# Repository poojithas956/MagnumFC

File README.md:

# MagnumFC

MagnumFC is my 30 × 30 mm flight-controller design, built in KiCad around an STM32F722RETx. Honestly? This project has been such a fun rabbit hole. I wanted to build a compact FPV controller that felt useful, clean, and a bit more intentional than a random stack of boards shoved together with duct-tape energy.

The idea is simple but kinda cool: keep the board small, give the IMU and power rails proper attention, and make a design that actually looks like it could become something real. Lowkey, I’m hyped about it because this is the kind of hardware project that turns into a whole obsession once the schematic starts to come together.

## Why I built this

I wanted a flight-controller board that felt compact without becoming a mess of routing and half-documented shortcuts. The plan was to include the essentials:

- STM32F722 main controller
- ICM-42688-P IMU
- BMP388 barometer
- ESP32-C3 coprocessor
- USB-C connection
- analog OSD support
- separate 5 V and 9 V supply rails

It’s the kind of project that feels slightly chaotic in the best way. You start with a few part choices, a rough concept, and then suddenly you’re deep in power rails, pin assignments, and the weird little details that decide whether a board is actually usable or just a pretty render.

## Design overview

| Component or section | Intended role |
| --- | --- |
| STM32F722RETx | Main flight-controller MCU |
| ICM-42688-P | SPI gyroscope and accelerometer |
| BMP388 | Barometer |
| ESP32-C3 | Wireless-connectivity coprocessor |
| W25N04KVZEIR | NAND flash shown in the schematic and PCB; confirm device support before enabling it in firmware |
| MP9943GQ-Z × 2 | Switching 9 V and 5 V rails |
| AP7361C and NCP167 | Separate digital and analog 3.3 V rails, as represented in the design |
| AT7456E | Analog OSD circuitry |
| USB-C | USB connection to the flight controller |

## Board renders

These images are KiCad renders and design screenshots, not photos of a manufactured board. So yes, they look sick, but they’re still just the design phase, not a fully proven hardware build.

More circuit and layout screenshots are in [`Screenshots/`](Screenshots/). The schematic is also available as [`docs/sch.pdf`](docs/sch.pdf).

## Firmware note

The files under [`firmware/`](firmware/) are an early Betaflight target configuration draft, not a compiled firmware image. That part is intentionally unfinished. I left motor output and onboard flash configuration unresolved instead of pretending everything is fine when it’s not.

## Repo structure

- [`PCB/`](PCB/) — KiCad schematic, PCB layout, custom libraries, and manufacturing exports
- [`production/`](production/) — BOM, placement, designators, netlist, and fabrication package
- [`firmware/`](firmware/) — early Betaflight target draft and validation notes
- [`Screenshots/`](Screenshots/) — design and layout images
- [`docs/`](docs/) — schematic PDF
- [`JOURNAL.md`](JOURNAL.md) — work journal and design notes

## LICENSE

MIT

### Happy forging!

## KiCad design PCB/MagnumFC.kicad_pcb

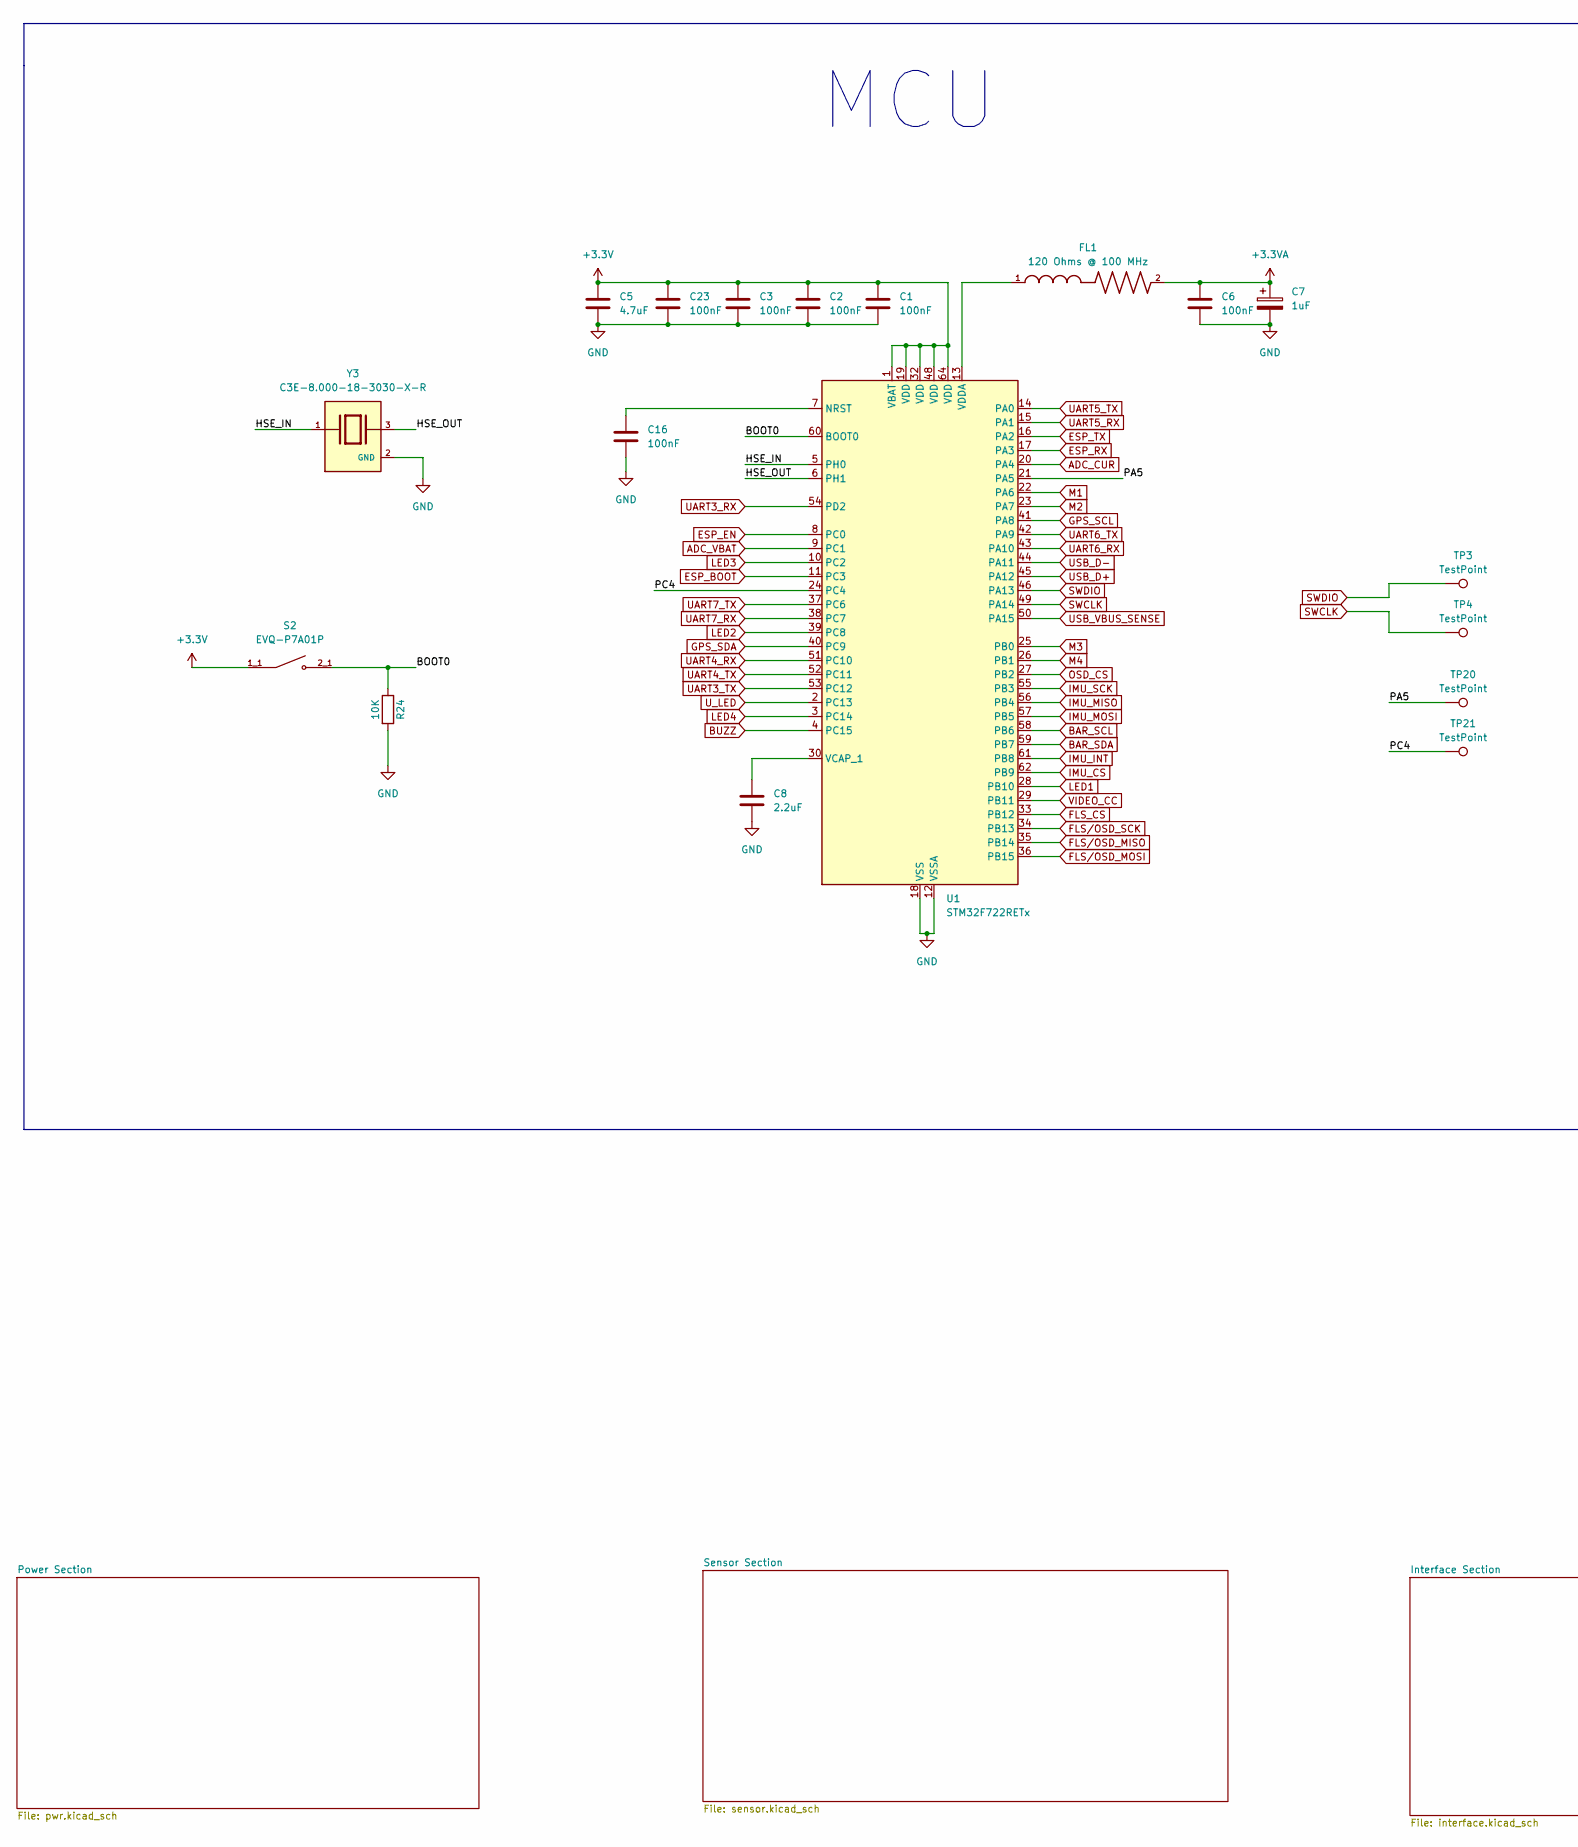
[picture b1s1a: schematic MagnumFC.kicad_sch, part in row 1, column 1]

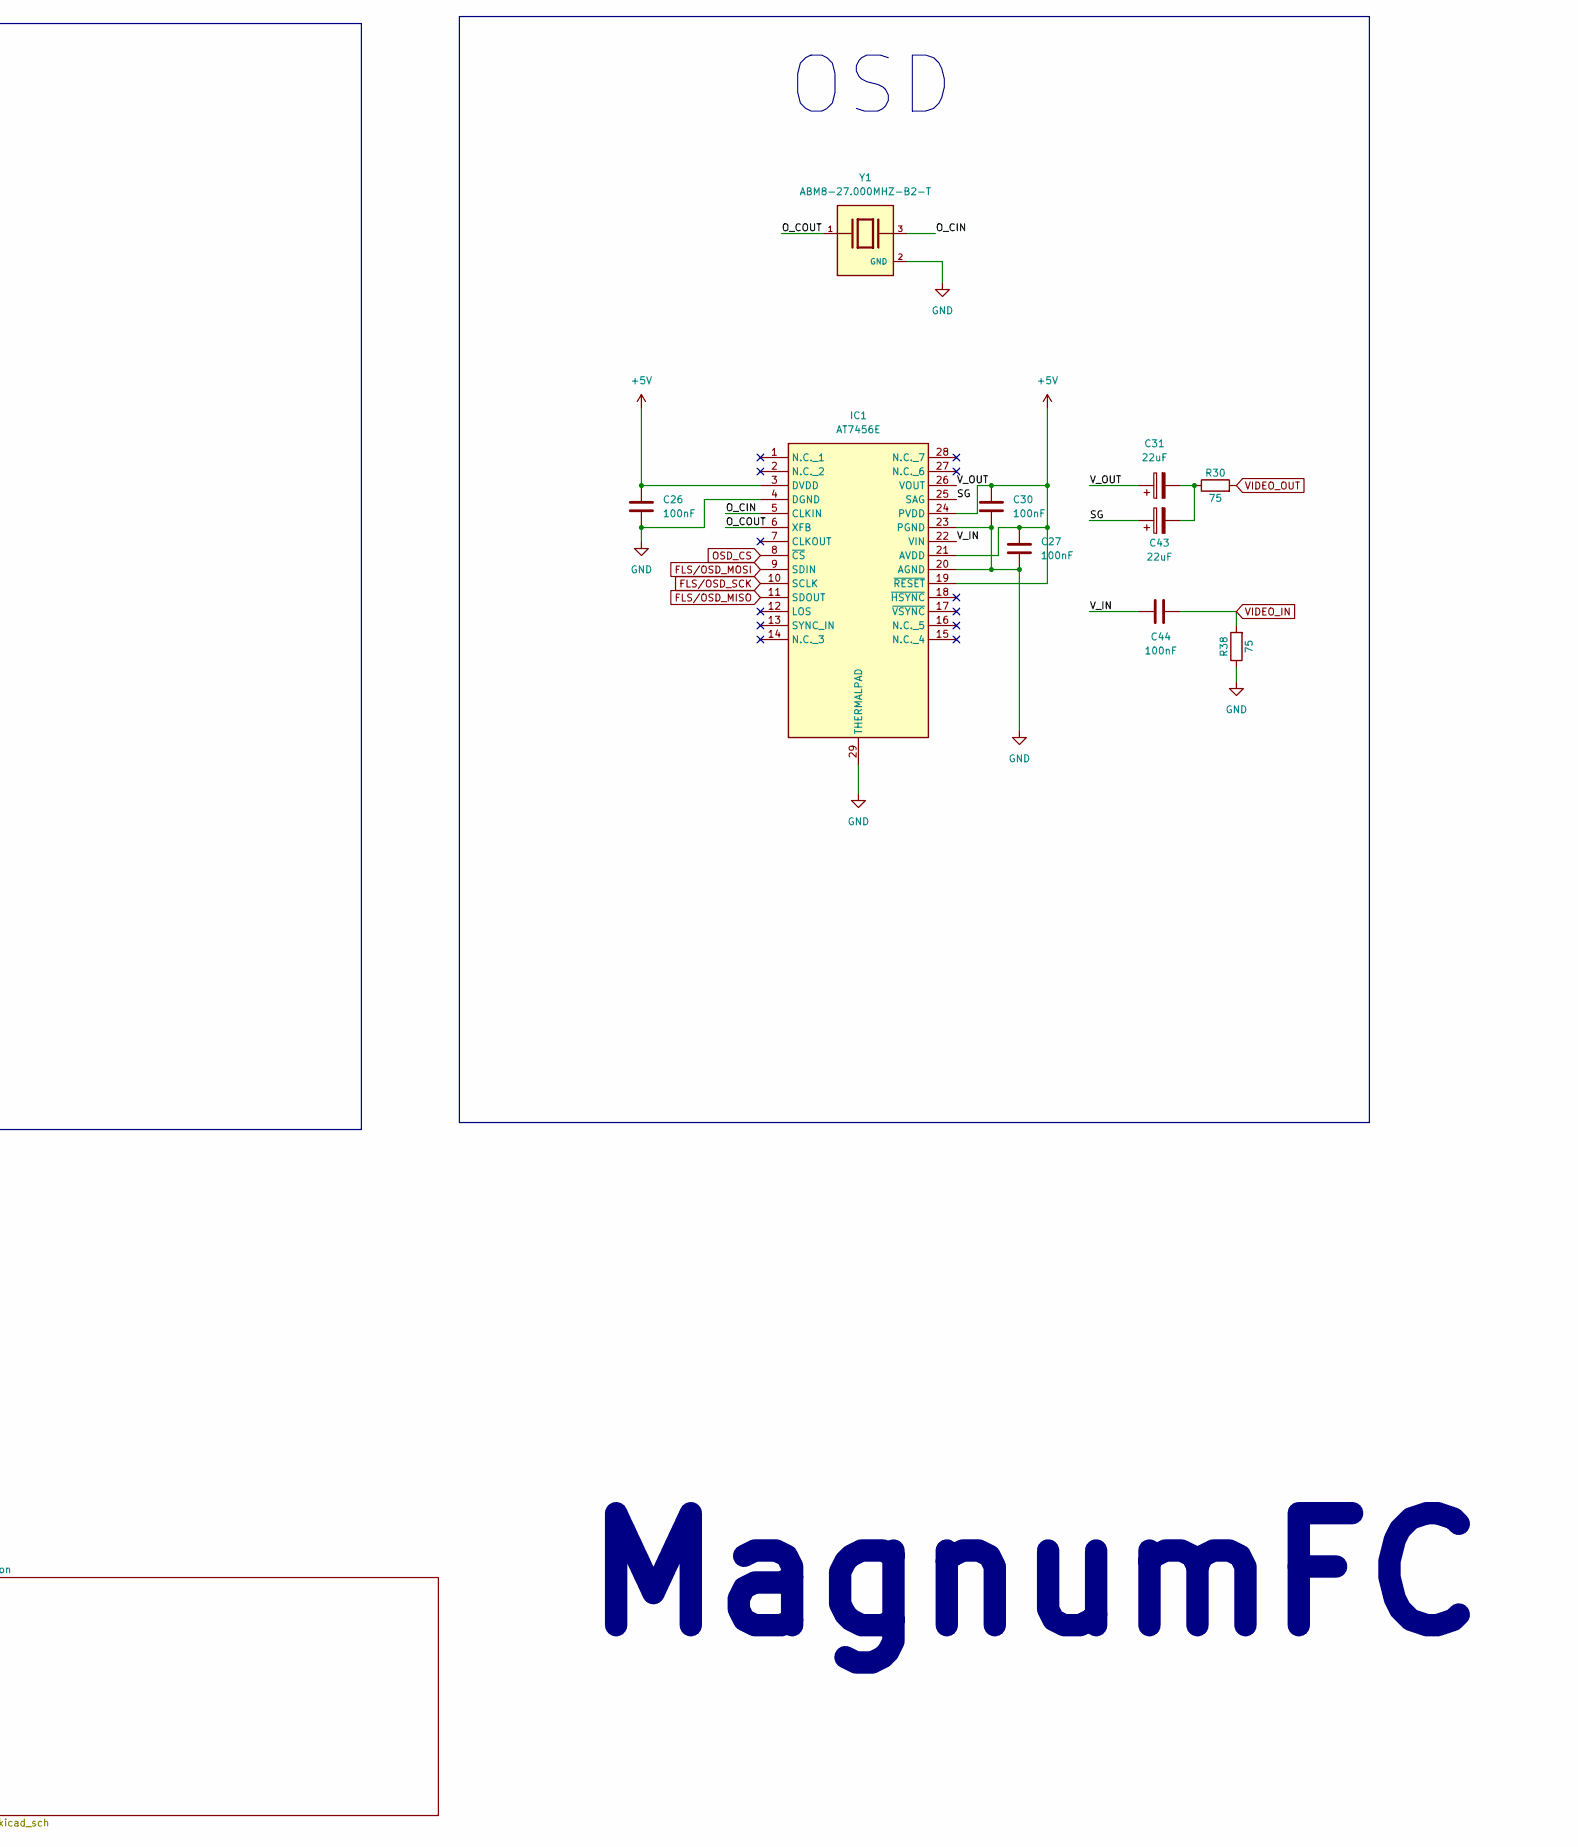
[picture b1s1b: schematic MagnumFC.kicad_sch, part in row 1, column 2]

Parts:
C1, C2, C3, C6, C16, C23, C26, C27, C30, C44: 100nF; C_0402_1005Metric; MANUFACTURER PART NUMBER CL05A104KA5NNNC; LCSC C100072
C5: 4.7uF; C_0603_1608Metric; MANUFACTURER PART NUMBER CL10A475KO8NNNC; LCSC C19666
C7: 1uF; C_0805_2012Metric; MANUFACTURER PART NUMBER CL21B105KOFNNNE; LCSC C24123
C8: 2.2uF; C_0402_1005Metric; MANUFACTURER PART NUMBER CL05A225KP5NSNC; LCSC C107369
C31, C43: 22uF; C_0805_2012Metric; MANUFACTURER PART NUMBER HGC0805R5226M350NSLJ; LCSC C22367832
FL1: 120 Ohms @ 100 MHz; L_0402_1005Metric; MANUFACTURER PART NUMBER MPZ1005S121CT000; LCSC C107331
IC1: AT7456E; SOP65P640X120-29N; Manufacturer_Part_Number AT7456E; LCSC C82351
R24: 10K; R_0402_1005Metric; MANUFACTURER PART NUMBER RC0402JR-0710KL; LCSC C60489
R30, R38: 75; R_0402_1005Metric; MANUFACTURER PART NUMBER RC0402JR-0775RL; LCSC C137841
S2: EVQ-P7A01P; SW_EVQ-P7A01P; PARTREV 2022.4; LCSC C79167
TP3, TP4, TP20, TP21: TestPoint; TestPoint_Pad_D1.0mm
U1: STM32F722RETx; LQFP-64_10x10mm_P0.5mm; MANUFACTURER PART NUMBER STM32F722RET6; LCSC C118207
Y1: ABM8-27.000MHZ-B2-T; XTAL_ABM8-27.000MHZ-B2-T; PARTREV 44041; LCSC C1985251
Y3: C3E-8.000-18-3030-X-R; XTAL_C3E-8.000-18-3030-X-R; PARTREV August 01, 2022; LCSC C2682775

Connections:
+3.3V: C1.1, C2.1, C3.1, C5.1, C23.1, S2.1_1, S2.1_2, U1.1 (VBAT), U1.19 (VDD), U1.32 (VDD), U1.48 (VDD), U1.64 (VDD); also elsewhere on the board
+3.3VA: C6.1, C7.1, FL1.2; also elsewhere on the board
+5V: C26.1, C27.1, C30.1, IC1.3 (DVDD), IC1.19 (~RESET), IC1.21 (AVDD), IC1.24 (PVDD); also elsewhere on the board
/BOOT0: R24.1, S2.2_1, S2.2_2, U1.60 (BOOT0)
/HSE_IN: U1.5 (PH0), Y3.1
/HSE_OUT: U1.6 (PH1), Y3.3
/O_CIN: IC1.5 (CLKIN), Y1.3
/O_COUT: IC1.6 (XFB), Y1.1
/PA5: TP20.1 (1_1), U1.21 (PA5)
/PC4: TP21.1 (1_1), U1.24 (PC4)
/SG: C43.1, IC1.25 (SAG)
/V_IN: C44.1, IC1.22 (VIN)
/V_OUT: C31.1, IC1.26 (VOUT)
ADC_CUR: U1.20 (PA4); also elsewhere on the board
ADC_VBAT: U1.9 (PC1); also elsewhere on the board
BAR_SCL: U1.58 (PB6); also elsewhere on the board
BAR_SDA: U1.59 (PB7); also elsewhere on the board
BUZZ: U1.4 (PC15); also elsewhere on the board
ESP_BOOT: U1.11 (PC3); also elsewhere on the board
ESP_EN: U1.8 (PC0); also elsewhere on the board
ESP_RX: U1.17 (PA3); also elsewhere on the board
ESP_TX: U1.16 (PA2); also elsewhere on the board
FLS_CS: U1.33 (PB12); also elsewhere on the board
FLS/OSD_MISO: IC1.11 (SDOUT), U1.35 (PB14); also elsewhere on the board
FLS/OSD_MOSI: IC1.9 (SDIN), U1.36 (PB15); also elsewhere on the board
FLS/OSD_SCK: IC1.10 (SCLK), U1.34 (PB13); also elsewhere on the board
GND: C1.2, C2.2, C3.2, C5.2, C6.2, C7.2, C8.2, C16.2, C23.2, C26.2, C27.2, C30.2, IC1.4 (DGND), IC1.20 (AGND), IC1.23 (PGND), IC1.29 (THERMALPAD), R24.2, R38.1, U1.12 (VSSA), U1.18 (VSS), U1.31 (VSS), U1.47 (VSS), U1.63 (VSS), Y1.2 (GND), Y1.4 (GND), Y3.2 (GND), Y3.4 (GND); also elsewhere on the board
GPS_SCL: U1.41 (PA8); also elsewhere on the board
GPS_SDA: U1.40 (PC9); also elsewhere on the board
IMU_CS: U1.62 (PB9); also elsewhere on the board
IMU_INT: U1.61 (PB8); also elsewhere on the board
IMU_MISO: U1.56 (PB4); also elsewhere on the board
IMU_MOSI: U1.57 (PB5); also elsewhere on the board
IMU_SCK: U1.55 (PB3); also elsewhere on the board
LED1: U1.28 (PB10); also elsewhere on the board
LED2: U1.39 (PC8); also elsewhere on the board
LED3: U1.10 (PC2); also elsewhere on the board
LED4: U1.3 (PC14); also elsewhere on the board
M1: U1.22 (PA6); also elsewhere on the board
M2: U1.23 (PA7); also elsewhere on the board
M3: U1.25 (PB0); also elsewhere on the board
M4: U1.26 (PB1); also elsewhere on the board
unnamed: C31.2, C43.2, R30.1
unnamed: C16.1, U1.7 (NRST)
unnamed: C8.1, U1.30 (VCAP_1)
unnamed: FL1.1, U1.13 (VDDA)
OSD_CS: IC1.8 (~CS), U1.27 (PB2)
SWCLK: TP4.1 (1_1), U1.49 (PA14)
SWDIO: TP3.1 (1_1), U1.46 (PA13)
UART3_RX: U1.54 (PD2); also elsewhere on the board
UART3_TX: U1.53 (PC12); also elsewhere on the board
UART4_RX: U1.51 (PC10); also elsewhere on the board
UART4_TX: U1.52 (PC11); also elsewhere on the board
UART5_RX: U1.15 (PA1); also elsewhere on the board
UART5_TX: U1.14 (PA0); also elsewhere on the board
UART6_RX: U1.43 (PA10)
UART6_TX: U1.42 (PA9)
UART7_RX: U1.38 (PC7); also elsewhere on the board
UART7_TX: U1.37 (PC6); also elsewhere on the board
USB_D+: U1.45 (PA12); also elsewhere on the board
USB_D-: U1.44 (PA11); also elsewhere on the board
USB_VBUS_SENSE: U1.50 (PA15); also elsewhere on the board
U_LED: U1.2 (PC13); also elsewhere on the board
VIDEO_CC: U1.29 (PB11); also elsewhere on the board
VIDEO_IN: C44.2, R38.2; also elsewhere on the board
VIDEO_OUT: R30.2; also elsewhere on the board

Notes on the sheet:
MagnumFC
MCU
OSD

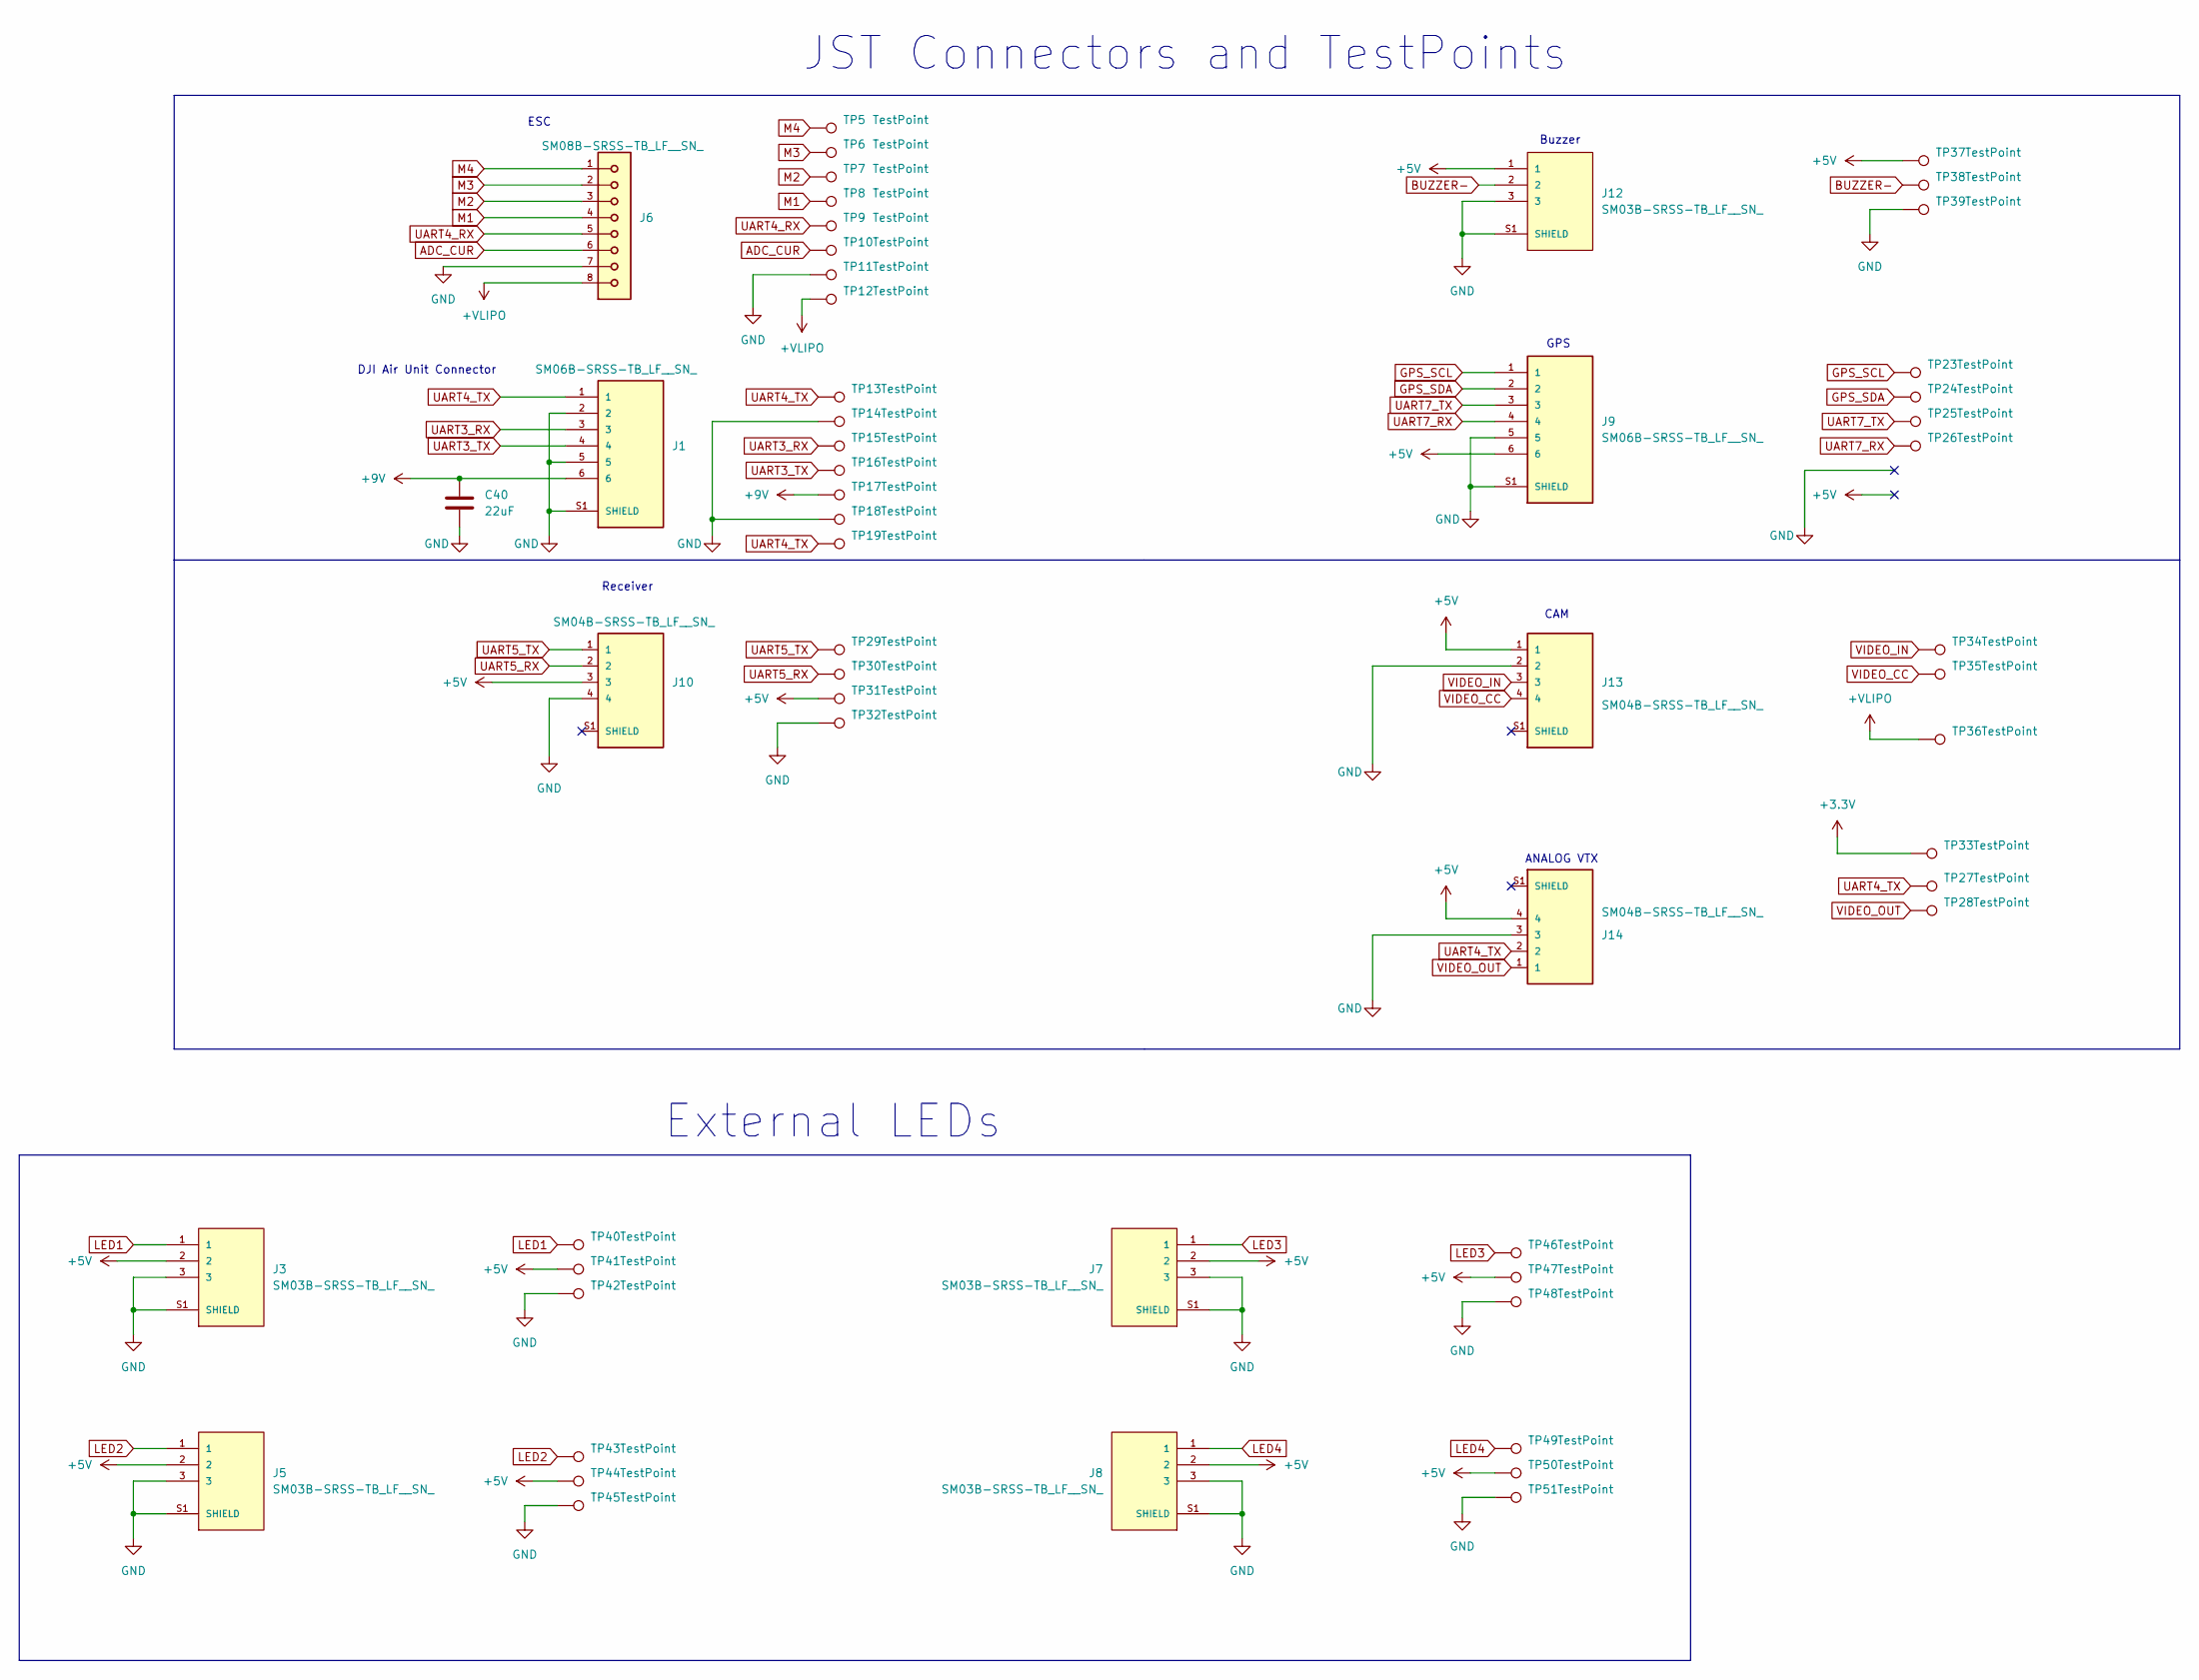
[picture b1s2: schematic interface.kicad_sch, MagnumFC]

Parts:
C40: 22uF; C_0805_2012Metric; MANUFACTURER PART NUMBER HGC0805R5226M350NSLJ; LCSC C22367832
J1, J9: SM06B-SRSS-TB_LF__SN_; JST_SM06B-SRSS-TB_LF__SN_; MANUFACTURER PART NUMBER HC-1.0-6PWT; LCSC C2845365
J3, J5, J7, J8, J12: SM03B-SRSS-TB_LF__SN_; JST_SM03B-SRSS-TB_LF__SN_; MANUFACTURER PART NUMBER HC-1.0-3PWT; LCSC C2845362
J6: SM08B-SRSS-TB_LF__SN_; JST_SM08B-SRSS-TB_LF__SN_; MANUFACTURER PART NUMBER SM08B-SRSS-TB(LF)(SN); LCSC C160407
J10, J13, J14: SM04B-SRSS-TB_LF__SN_; JST_SM04B-SRSS-TB_LF__SN_; MANUFACTURER PART NUMBER HC-1.0-4PWT; LCSC C2845363
TP5, TP6, TP7, TP8, TP9, TP10, TP40, TP41, TP42, TP43, TP44, TP45, TP46, TP47, TP48, TP49, TP50, TP51: TestPoint; TestPoint_Pad_D1.0mm
TP11, TP12: TestPoint; TestPoint_Pad_D2.0mm
TP13, TP14, TP15, TP16, TP18, TP19, TP23, TP24, TP25, TP26, TP27, TP28, TP29, TP30, TP32, TP33, TP34, TP35, TP36, TP38, TP39: TestPoint; TestPoint_Pad_1.0x1.0mm
TP17, TP31, TP37: TestPoint; TestPoint_Pad_2.0x2.0mm

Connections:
+3.3V: TP33.1 (1_1); also elsewhere on the board
+5V: J3.2, J5.2, J7.2, J8.2, J9.6, J10.3, J12.1, J13.1, J14.4, TP31.1 (1_1), TP37.1 (1_1), TP41.1 (1_1), TP44.1 (1_1), TP47.1 (1_1), TP50.1 (1_1); also elsewhere on the board
+9V: C40.1, J1.6, TP17.1 (1_1); also elsewhere on the board
+VLIPO: J6.8, TP12.1 (1_1), TP36.1 (1_1); also elsewhere on the board
ADC_CUR: J6.6, TP10.1 (1_1); also elsewhere on the board
BUZZER-: J12.2, TP38.1 (1_1); also elsewhere on the board
GND: C40.2, J1.2, J1.5, J1.S1 (SHIELD), J1.S2 (SHIELD), J3.3, J3.S1 (SHIELD), J3.S2 (SHIELD), J5.3, J5.S1 (SHIELD), J5.S2 (SHIELD), J6.7, J7.3, J7.S1 (SHIELD), J7.S2 (SHIELD), J8.3, J8.S1 (SHIELD), J8.S2 (SHIELD), J9.5, J9.S1 (SHIELD), J9.S2 (SHIELD), J10.4, J12.3, J12.S1 (SHIELD), J12.S2 (SHIELD), J13.2, J14.3, TP11.1 (1_1), TP14.1 (1_1), TP18.1 (1_1), TP32.1 (1_1), TP39.1 (1_1), TP42.1 (1_1), TP45.1 (1_1), TP48.1 (1_1), TP51.1 (1_1); also elsewhere on the board
GPS_SCL: J9.1, TP23.1 (1_1); also elsewhere on the board
GPS_SDA: J9.2, TP24.1 (1_1); also elsewhere on the board
LED1: J3.1, TP40.1 (1_1); also elsewhere on the board
LED2: J5.1, TP43.1 (1_1); also elsewhere on the board
LED3: J7.1, TP46.1 (1_1); also elsewhere on the board
LED4: J8.1, TP49.1 (1_1); also elsewhere on the board
M1: J6.4, TP8.1 (1_1); also elsewhere on the board
M2: J6.3, TP7.1 (1_1); also elsewhere on the board
M3: J6.2, TP6.1 (1_1); also elsewhere on the board
M4: J6.1, TP5.1 (1_1); also elsewhere on the board
UART3_RX: J1.3, TP15.1 (1_1); also elsewhere on the board
UART3_TX: J1.4, TP16.1 (1_1); also elsewhere on the board
UART4_RX: J6.5, TP9.1 (1_1); also elsewhere on the board
UART4_TX: J1.1, J14.2, TP13.1 (1_1), TP19.1 (1_1), TP27.1 (1_1); also elsewhere on the board
UART5_RX: J10.2, TP30.1 (1_1); also elsewhere on the board
UART5_TX: J10.1, TP29.1 (1_1); also elsewhere on the board
UART7_RX: J9.4, TP26.1 (1_1); also elsewhere on the board
UART7_TX: J9.3, TP25.1 (1_1); also elsewhere on the board
VIDEO_CC: J13.4, TP35.1 (1_1); also elsewhere on the board
VIDEO_IN: J13.3, TP34.1 (1_1); also elsewhere on the board
VIDEO_OUT: J14.1, TP28.1 (1_1); also elsewhere on the board

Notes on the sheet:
ANALOG VTX
External LEDs
Buzzer
DJI Air Unit Connector
GPS
JST Connectors and TestPoints
ESC
Receiver
CAM

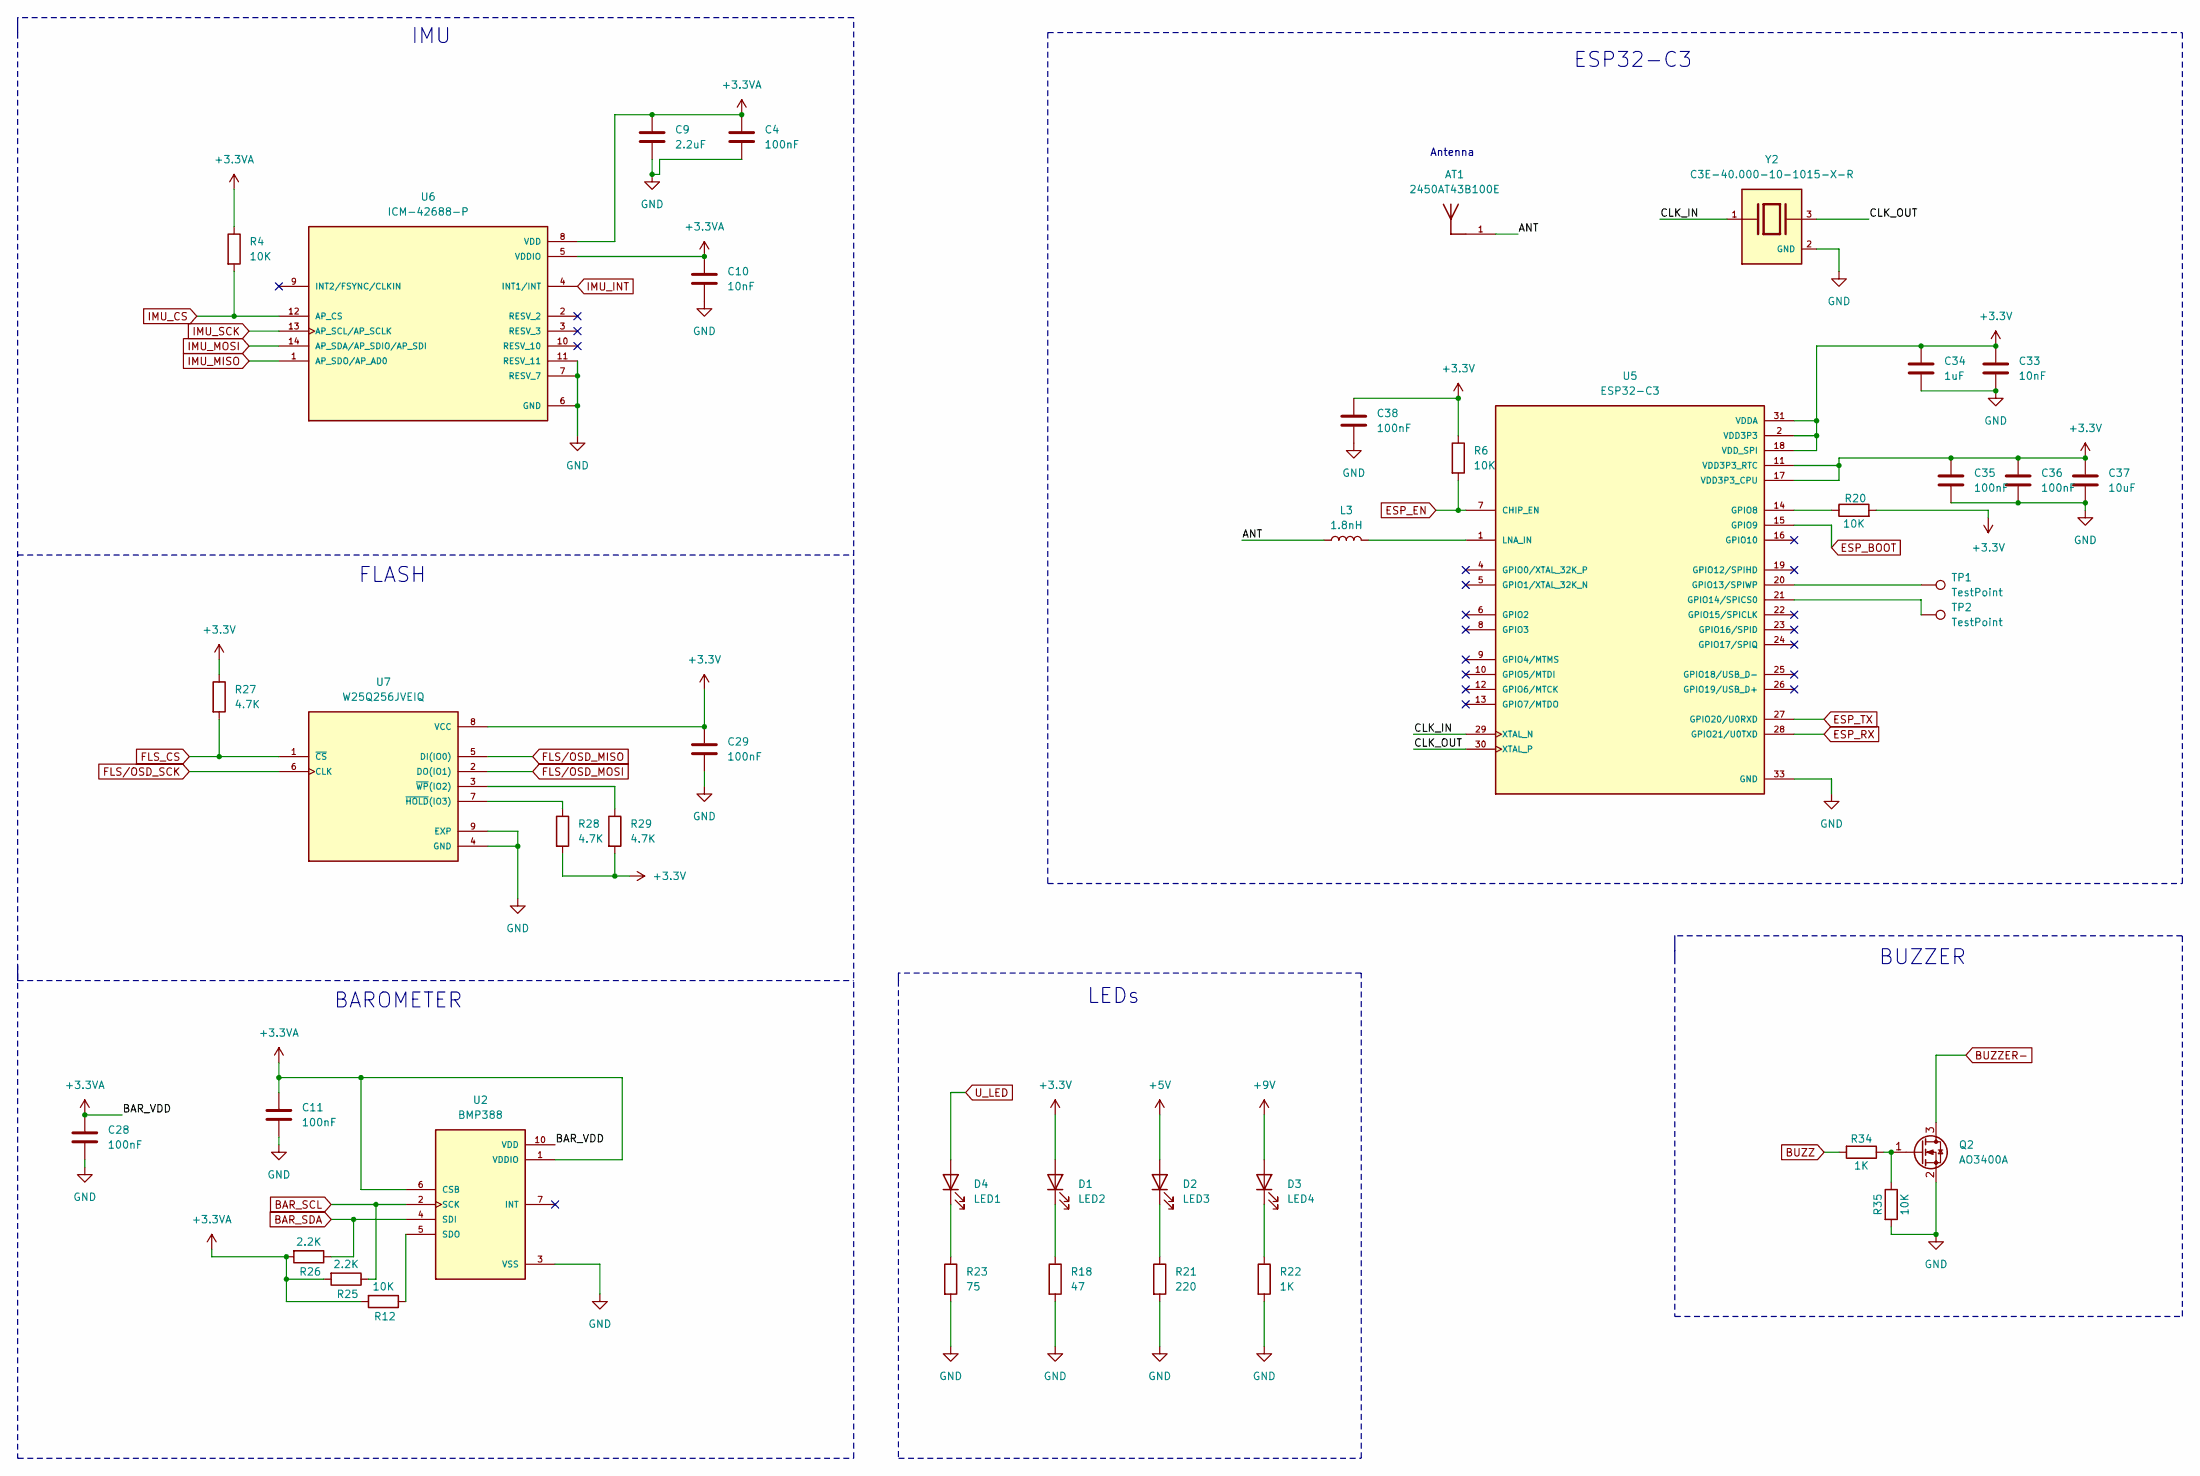
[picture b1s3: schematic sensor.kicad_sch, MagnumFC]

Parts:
AT1: 2450AT43B100E; ANTENNA_2450AT43B100E; PARTREV N/A; LCSC C2917721
C4, C11, C28, C29, C35, C36, C38: 100nF; C_0402_1005Metric; MANUFACTURER PART NUMBER CL05A104KA5NNNC; LCSC C100072
C9: 2.2uF; C_0402_1005Metric; MANUFACTURER PART NUMBER CL05A225KP5NSNC; LCSC C107369
C10, C33: 10nF; C_0402_1005Metric; MANUFACTURER PART NUMBER CL05B103KB5NNNC; LCSC C15195
C34: 1uF; C_0402_1005Metric; MANUFACTURER PART NUMBER CL05A105KO5NNNC; LCSC C29266
C37: 10uF; C_0805_2012Metric; MANUFACTURER PART NUMBER CL21A106KBYQNNE; LCSC C2932476
D1: LED2; LED_0805_2012Metric; MANUFACTURER PART NUMBER KT-0805B; LCSC C2293
D2: LED3; LED_0805_2012Metric; MANUFACTURER PART NUMBER KT-0805Y; LCSC C2296
D3: LED4; LED_0805_2012Metric; MANUFACTURER PART NUMBER KT-0805G; LCSC C2297
D4: LED1; LED_0805_2012Metric; MANUFACTURER PART NUMBER KT-0805R; LCSC C2295
L3: 1.8nH; L_0402_1005Metric; MANUFACTURER PART NUMBER LQG15HS1N8S02D; LCSC C77107
Q2: AO3400A; SOT-23; MANUFACTURER PART NUMBER AO3400A; LCSC C20917
R4, R6, R12, R20, R35: 10K; R_0402_1005Metric; MANUFACTURER PART NUMBER RC0402JR-0710KL; LCSC C60489
R18: 47; R_0402_1005Metric; MANUFACTURER PART NUMBER RC0402FR-0747RL; LCSC C137973
R21: 220; R_0402_1005Metric; MANUFACTURER PART NUMBER RC0402FR-07220RL; LCSC C112291
R22, R34: 1K; R_0402_1005Metric; MANUFACTURER PART NUMBER RC0402FR-071KL; LCSC C106235
R23: 75; R_0402_1005Metric; MANUFACTURER PART NUMBER RC0402JR-0775RL; LCSC C137841
R25, R26: 2.2K; R_0402_1005Metric; MANUFACTURER PART NUMBER RC0402JR-072K2L; LCSC C163447
R27, R28, R29: 4.7K; R_0402_1005Metric; MANUFACTURER PART NUMBER RC0402FR-074K7L; LCSC C105871
TP1, TP2: TestPoint; TestPoint_Pad_D1.0mm
U2: BMP388; XDCR_BMP388; PARTREV 1.7; LCSC C779278
U5: ESP32-C3; QFN50P500X500X90-33N; PARTREV 2.0; LCSC C2838500
U6: ICM-42688-P; PQFN50P300X250X97-14N; PARTREV 1.2; LCSC C1850418, Mouser No: 410-ICM-42688-P
U7: W25Q256JVEIQ; IC_W25N04KVZEIR; PARTREV I; LCSC C97522
Y2: C3E-40.000-10-1015-X-R; XTAL_C3E-40.000-10-1015-X-R; PARTREV August 01, 2022; LCSC C5444549

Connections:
+3.3V: C29.1, C33.1, C34.1, C35.1, C36.1, C37.1, C38.1, D1.2 (A), R6.1, R20.2, R27.1, R28.2, R29.2, U5.2 (VDD3P3), U5.3 (VDD3P3), U5.11 (VDD3P3_RTC), U5.17 (VDD3P3_CPU), U5.18 (VDD_SPI), U5.31 (VDDA), U5.32 (VDDA), U7.8 (VCC); also elsewhere on the board
+3.3VA: C4.1, C9.1, C10.1, C11.1, C28.1, R4.1, R12.2, R25.2, R26.2, U2.1 (VDDIO), U2.6 (CSB), U2.10 (VDD), U6.5 (VDDIO), U6.8 (VDD); also elsewhere on the board
+5V: D2.2 (A); also elsewhere on the board
+9V: D3.2 (A); also elsewhere on the board
/Sensor Section/ANT: AT1.1, L3.1
/Sensor Section/CLK_IN: U5.29 (XTAL_N), Y2.1
/Sensor Section/CLK_OUT: U5.30 (XTAL_P), Y2.3
BAR_SCL: R25.1, U2.2 (SCK); also elsewhere on the board
BAR_SDA: R26.1, U2.4 (SDI); also elsewhere on the board
BUZZ: R34.2; also elsewhere on the board
BUZZER-: Q2.3 (D); also elsewhere on the board
ESP_BOOT: U5.15 (GPIO9); also elsewhere on the board
ESP_EN: R6.2, U5.7 (CHIP_EN); also elsewhere on the board
ESP_RX: U5.28 (GPIO21/U0TXD); also elsewhere on the board
ESP_TX: U5.27 (GPIO20/U0RXD); also elsewhere on the board
FLS_CS: R27.2, U7.1 (~CS); also elsewhere on the board
FLS/OSD_MISO: U7.5 (DI(IO0)); also elsewhere on the board
FLS/OSD_MOSI: U7.2 (DO(IO1)); also elsewhere on the board
FLS/OSD_SCK: U7.6 (CLK); also elsewhere on the board
GND: C4.2, C9.2, C10.2, C11.2, C28.2, C29.2, C33.2, C34.2, C35.2, C36.2, C37.2, C38.2, Q2.2 (S), R18.2, R21.2, R22.2, R23.2, R35.2, U2.3 (VSS), U2.8 (VSS), U2.9 (VSS), U5.33 (GND), U6.6 (GND), U6.7 (RESV_7), U6.11 (RESV_11), U7.4 (GND), U7.9 (EXP), Y2.2 (GND), Y2.4 (GND); also elsewhere on the board
IMU_CS: R4.2, U6.12 (AP_CS); also elsewhere on the board
IMU_INT: U6.4 (INT1/INT); also elsewhere on the board
IMU_MISO: U6.1 (AP_SDO/AP_AD0); also elsewhere on the board
IMU_MOSI: U6.14 (AP_SDA/AP_SDIO/AP_SDI); also elsewhere on the board
IMU_SCK: U6.13 (AP_SCL/AP_SCLK); also elsewhere on the board
unnamed: D1.1 (K), R18.1
unnamed: D2.1 (K), R21.1
unnamed: D3.1 (K), R22.1
unnamed: D4.1 (K), R23.1
unnamed: Q2.1 (G), R34.1, R35.1
unnamed: R12.1, U2.5 (SDO)
unnamed: R20.1, U5.14 (GPIO8)
unnamed: TP1.1 (1_1), U5.20 (GPIO13/SPIWP)
unnamed: TP2.1 (1_1), U5.21 (GPIO14/SPICS0)
unnamed: L3.2, U5.1 (LNA_IN)
unnamed: R28.1, U7.7 (~HOLD(IO3))
unnamed: R29.1, U7.3 (~WP(IO2))
U_LED: D4.2 (A); also elsewhere on the board

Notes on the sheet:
FLASH
BUZZER
BAROMETER
LEDs
IMU
ESP32-C3
Antenna
